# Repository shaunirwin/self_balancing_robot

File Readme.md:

# Self-balancing robot

Welcome to the project page for the self-balancing robot!

## Objectives

The goal of this project is to develop a robotic platform that can serve as a fun way to explore various aspects of robotics, including classical and learning-based control, 3D vision, sensor fusion and modelling.

## Status

The robot has been built and is currently using PID control for pitch control. Pitch estimation works well. I am busy simulating the system and improving the controller using classical control methods.

Once I am satisfied with the classical controller (both PID and LQR), I will move onto the next phase of learning-based control.

## Project layout

- [Firmware](firmware/platformio_projects/self_balancing_robot/README.md): ESP32 controller, HTTP API, and PC serial reader. Earlier ESP-IDF work is in `firmware/archived/`.
- [Laptop dashboard](software/webserver/README.md): live controls and recording viewer.
- [Python scripts and simulation](software/python/README.md): calibration, plotting, recording conversion, and MuJoCo model.
- [Electronics](electronics/robot_pcb/): KiCad PCB files; [cable harnesses](electronics/cable_harnesses/README.md) are alongside them.
- [Mechanical design](mechanical/Readme.md): Onshape CAD link and printing notes.
- [Recorded data](data/data_logs/README.md): logs and example recordings; older data is in `data/archive/`.
- [Documentation](documentation/): supporting figures.

The robot sitting in its harness:

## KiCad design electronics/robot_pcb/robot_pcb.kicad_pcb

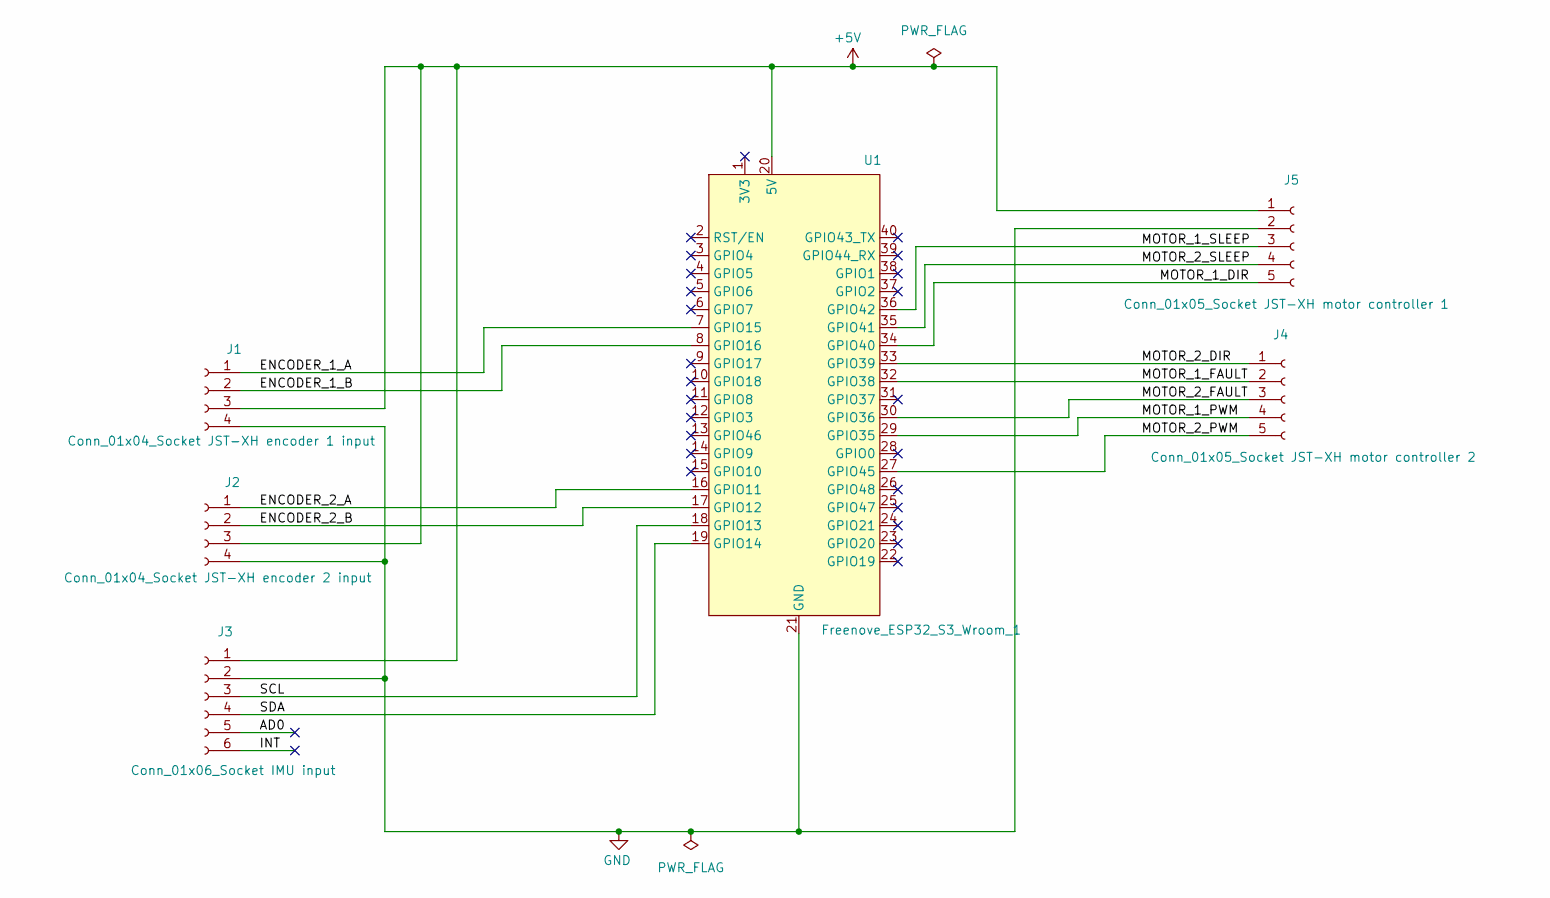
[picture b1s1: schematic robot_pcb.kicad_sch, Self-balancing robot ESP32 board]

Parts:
J1: Conn_01x04_Socket JST-XH encoder 1 input; PinSocket_1x04_P2.54mm_Vertical
J2: Conn_01x04_Socket JST-XH encoder 2 input; PinSocket_1x04_P2.54mm_Vertical
J3: Conn_01x06_Socket IMU input; PinSocket_1x06_P2.54mm_Vertical
J4: Conn_01x05_Socket JST-XH motor controller 2; PinSocket_1x05_P2.54mm_Vertical
J5: Conn_01x05_Socket JST-XH motor controller 1; PinSocket_1x05_P2.54mm_Vertical
U1: Freenove_ESP32_S3_Wroom_1; freenove_esp32_s3_wroom

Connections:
+5V: J1.3, J2.3, J3.1, J5.1, U1.20 (5V)
/AD0: J3.5
/ENCODER_1_A: J1.1, U1.7 (GPIO15)
/ENCODER_1_B: J1.2, U1.8 (GPIO16)
/ENCODER_2_A: J2.1, U1.16 (GPIO11)
/ENCODER_2_B: J2.2, U1.17 (GPIO12)
/INT: J3.6
/MOTOR_1_DIR: J5.5, U1.34 (GPIO40)
/MOTOR_1_FAULT: J4.2, U1.32 (GPIO38)
/MOTOR_1_PWM: J4.4, U1.29 (GPIO35)
/MOTOR_1_SLEEP: J5.3, U1.36 (GPIO42)
/MOTOR_2_DIR: J4.1, U1.33 (GPIO39)
/MOTOR_2_FAULT: J4.3, U1.30 (GPIO36)
/MOTOR_2_PWM: J4.5, U1.27 (GPIO45)
/MOTOR_2_SLEEP: J5.4, U1.35 (GPIO41)
/SCL: J3.3, U1.18 (GPIO13)
/SDA: J3.4, U1.19 (GPIO14)
GND: J1.4, J2.4, J3.2, J5.2, U1.21 (GND)

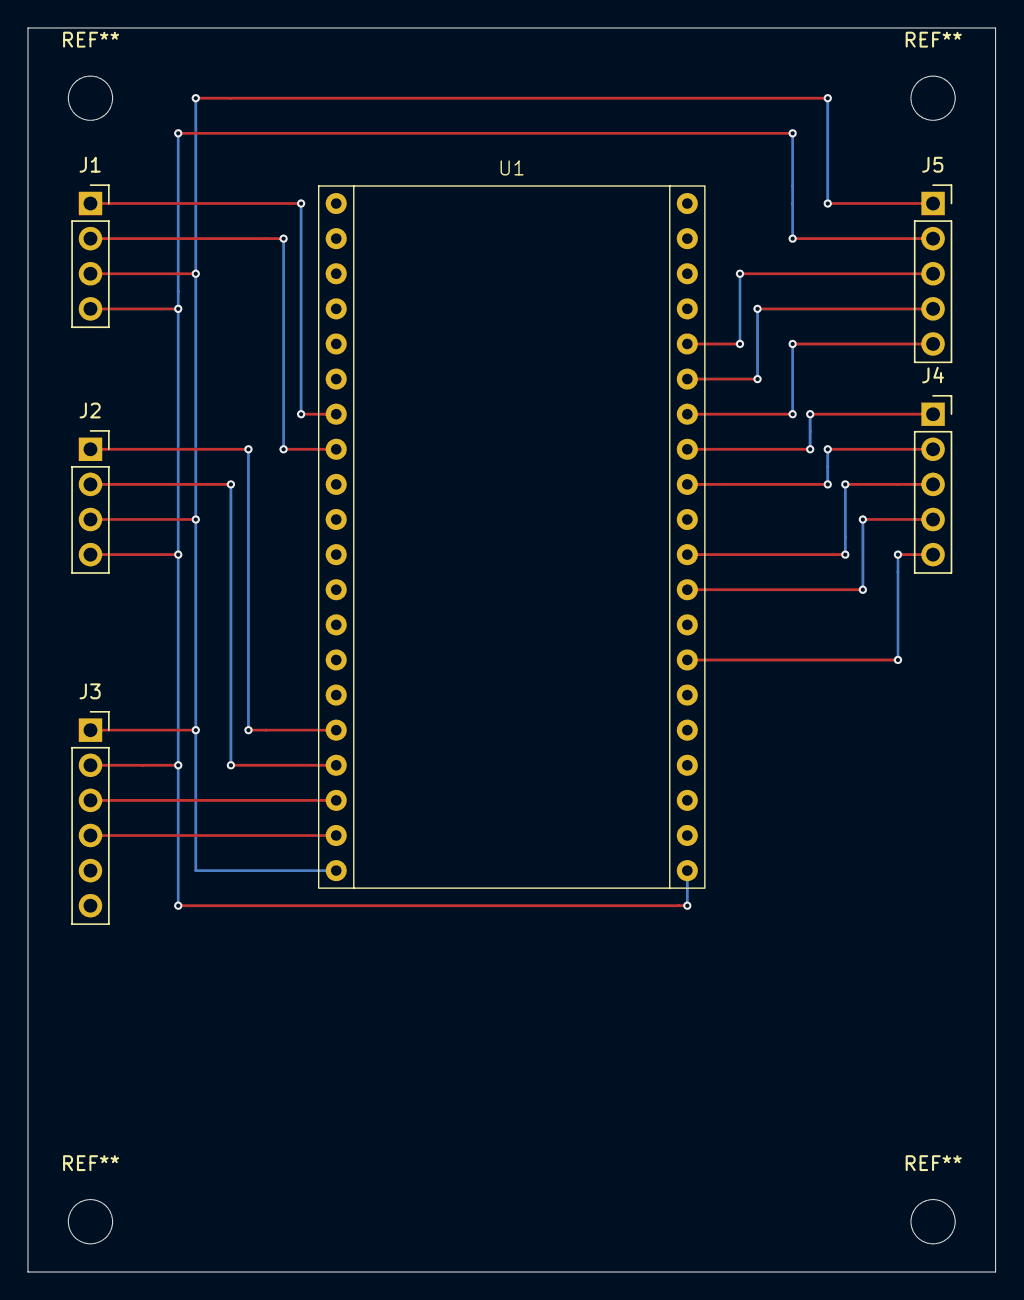
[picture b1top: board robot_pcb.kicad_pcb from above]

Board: 2 copper layers, 70.0 x 90.0 mm, 6 parts (0 on the bottom side), 16 nets.

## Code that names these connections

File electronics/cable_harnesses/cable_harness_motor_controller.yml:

connectors:
  X1:
    type: IDC 2x20      # connector type C. Connects cable to the G2 motor board
    subtype: female
    pincount: 40
    pins: [2, 6, 15, 16, 18, 22, 29, 31, 32, 33]
    pinlabels: [5V, GND, MOTOR_1_SLEEP,  MOTOR_2_SLEEP, MOTOR_1_DIR, MOTOR_2_DIR, MOTOR_1_FAULT, MOTOR_2_FAULT, MOTOR_1_PWM, MOTOR_2_PWM]
  X2:
    type: JST-XH 5 pin    # connector type G1. Connects cable to the ESP32 board
    subtype: male
    pinlabels: [5V, GND, MOTOR_1_SLEEP,  MOTOR_2_SLEEP, MOTOR_1_DIR]
  X3:
    type: JST-XH 5 pin    # connector type G2. Connects cable to the ESP32 board
    subtype: male
    pinlabels: [MOTOR_2_DIR, MOTOR_1_FAULT, MOTOR_2_FAULT, MOTOR_1_PWM, MOTOR_2_PWM]
  X:                    # a fake connector as a hack, just to allow wireviz to connect wire bundles to one another without a connector in between
    style: simple
    autogenerate: true
    type: ""
    ignore_in_bom: true

cables:
  W1:       # cable harness 1a
    gauge: 0.25 mm2
    length: 0.2
    color_code: DIN
    wirecount: 10
    shield: false
  W2:       # cable harness 1b
    gauge: 0.25 mm2
    length: 0.2
    color_code: DIN
    wirecount: 5
    shield: false
  W3:       # cable harness 1c
    gauge: 0.25 mm2
    length: 0.2
    color_code: DIN
    wirecount: 5
    shield: false

connections:
  -
    - X1: [2, 6, 15, 16, 18]
    - W1: [1-5]
    - [X,X,X,X,X]             # fake connectors for the sake of wireviz
    - W2: [1-5]
    - X2: [1-5]
  -
    - X1: [22, 29, 31, 32, 33]
    - W1: [6-10]
    - [X,X,X,X,X]         # fake connectors for the sake of wireviz
    - W3: [1-5]
    - X3: [1-5]

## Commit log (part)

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2024-05-07 Add arduino sketches
2024-05-07 Add example cable harness wireviz
2024-05-07 Add kicad files
2024-05-09 Add cable harness yaml files
2024-05-09 Add gitignore to cable harness folder
2024-05-09 Update connectors for motor controller board
2024-05-09 Connect motor driver board to ESP32 board using two JST connectors
2024-05-10 Add PlatformIO initial code
2024-05-12 Finished ESP32 board schematic
2024-05-12 Add interrupts to measure quadrature encoder position and direction
2024-05-13 Motor encoder
2024-05-13 Send struct of 3 ints to python over serial
2024-05-13 Clean up
2024-05-19 Read IMU values into correct units
2024-05-19 Calculate pitch angle using raw accel readings, ignoring linear motion
2024-05-19 Add hardware timer at 250Hz
2024-05-19 Trigger FreeRTOS task at 250Hz using hardware timer
2024-05-19 Send data from task to task using queue
2024-05-19 Send raw IMU readings at 250Hz via serial
2024-05-19 Calculate gyro offset in python
2024-05-19 Add complementary filter
2024-05-19 Cleanup
2024-05-19 Implement complementary filter on ESP32
2024-05-21 Update pin locations for easier perf board soldering
2024-05-22 Update cable harnesses
2024-05-23 Zero gyro. Invert acceleromater readings due to sensor upside down
2024-05-23 Configure motor 2 pins
2024-05-23 Minor refactoring
2024-05-24 Control motors using pitch estimate!
2024-07-10 Wheel encoders working and sending pulse counts to python. Direction not yet sending correctly
2024-07-10 Send encoder pulses and convert to distance per wheel on python side
2024-07-11 Calculate and send velocity measurements from wheel encoders
2024-07-11 Fix wheel velocity measurements
2024-07-12 Print choice of data received over serial
2024-07-12 Send control packets and read into python
2024-07-12 PID Kp term working!
2024-07-12 Reduce top speed
2024-07-12 Switch motor direction and enable motors
2024-07-12 Cut off motors if pid output too low or pitch error exceeded
2024-07-13 Cut off motors if angle error really small
2024-07-13 Adjust PID settings
2024-07-13 Connect to WiFi. Read WiFi login info from secrets.h
2024-07-13 Add async web server that sets PID Kp term from post request
2024-07-13 Allow setting PID and other variables
2024-07-13 Update PID class when PID params change
2024-07-13 Add new PID classes that allow overriding derivative term with gyro readings
2024-07-13 Use doubles instead of floats in pid calcs
2024-07-13 Replace PID library to support D term input from raw gyro
2024-07-13 Add manual motor control
2024-07-13 Add python rest api client gui
2024-07-14 Toggle drive mode between auto and manual via gui
2024-07-14 Add endpoint to get status of all drive mode-related params
2024-07-14 Rename fields
2024-07-14 Prefill gui fields from robot current values
2024-07-14 Show angles in deg
2024-07-14 Use radio buttons to show motor dir
2024-07-14 Use enums for motor direction and control mode
2024-07-14 Add emergency stop button to gui
2024-07-14 Fix refreshing
2024-07-15 Display pitch angle current in gui
2024-07-15 Correct motor2 duty cycle to match motor 1 speed. Transmit serial every N packets
2024-07-17 Send packet ID and time since boot via serial
2024-08-06 Use float instead of doubles in pid
2024-08-06 Lower state estimator freq to 200Hz
2024-08-06 Log states to RAM with REST API
2025-02-01 Switch wheel encoder signals around for DFRobot motors
2025-02-01 Update estimator rate, wheel diameter
2025-02-01 Update pulses per rev for DFRobot motors
2025-02-01 Add uv package management
2025-02-03 Add serial read script
2025-02-03 Works for receiving !X@ message, where X is a single char
2025-02-03 Write strcut and read in c++
2025-02-03 Send and receive header packet
2025-02-03 Send and receive state estimate packet
2025-02-04 Get wheel encoders working
2025-02-04 Plot wheel encoder speed
2025-02-04 Add robot code readme
2025-02-04 Update other readme
2025-02-06 Send gyro calib data over serial
2025-02-07 Set 1400 pulses per rev encoders
2025-02-07 Update wheel encoder calib values
2025-02-07 Calculate gyro offset using average
2025-02-07 Refactor structs into header file
2025-02-07 Read temp. Separate structs for raw and processed IMU data
2025-02-07 Calibrate accel
2025-02-07 Send serial at 100Hz
2025-02-07 Log IMU values to binary file
2025-02-08 Turn off motors until IMU calibrated
2025-02-08 Zero pitch setpoint and change pwm ranges
2025-02-08 Using templated type to log data
2025-02-08 Prevent duplication of constants
2025-02-08 Use cmath library pi
2025-02-08 Refactor motor control structs
2025-02-08 Refactor motor control task into functions
2025-02-08 Only calculate PID if needed
2025-02-08 Add function to step motors
2025-02-08 Write to CSV
2025-02-08 Fixes to writing CSVs
2025-02-08 Fix matplotlib plotting issue
2025-02-08 Install mujoco
2025-02-10 Calculate lagrangian using sympy
2025-02-12 Lagrangian calc fixes
2025-02-16 Add main readme and pic
2025-02-16 Make image smaller
2025-02-16 Add link to onshape
2025-02-16 Fix path
2025-02-16 Fix links
2025-02-16 Fix link
2025-02-16 Remove python serial plotting
    We are now using the new and improved C++ serial comms script
2025-02-16 Remove unused arduino code
2025-02-16 Readme
2025-02-18 Fix 2nd euler lagrange equation. 1st might still be wrong
2025-02-18 Fix euler lagrange equations
2025-02-18 Remove method 1
2025-02-20 Simulate motor as first order linear ode
2025-02-20 Add pwm calib script
2025-02-20 Simulate closed loop sheel speed controller
2025-02-21 Create initial PI controller
2025-02-24 Add minimal esp-idf example project that builds and flashes
2025-02-24 Get LED to blink using ESP-IDF
2025-02-24 Add readme for ESP-IDF project
2025-02-24 Add data structs. Need to convert to c-compatible types
2025-02-24 Write struct over serial
2025-03-09 Convert to C++
2025-03-09 Add data struct header file
2025-03-09 Fix header file types
2025-03-09 Copy data struct header files to have same content
2025-03-09 Point to same data structs header
2025-03-09 Send current time in header packet
2025-03-09 Create new packets every time step
2025-03-09 Include pulse_cnt library
2025-03-09 Get pulse cnt example code compiling. Not yet suited to my needs
